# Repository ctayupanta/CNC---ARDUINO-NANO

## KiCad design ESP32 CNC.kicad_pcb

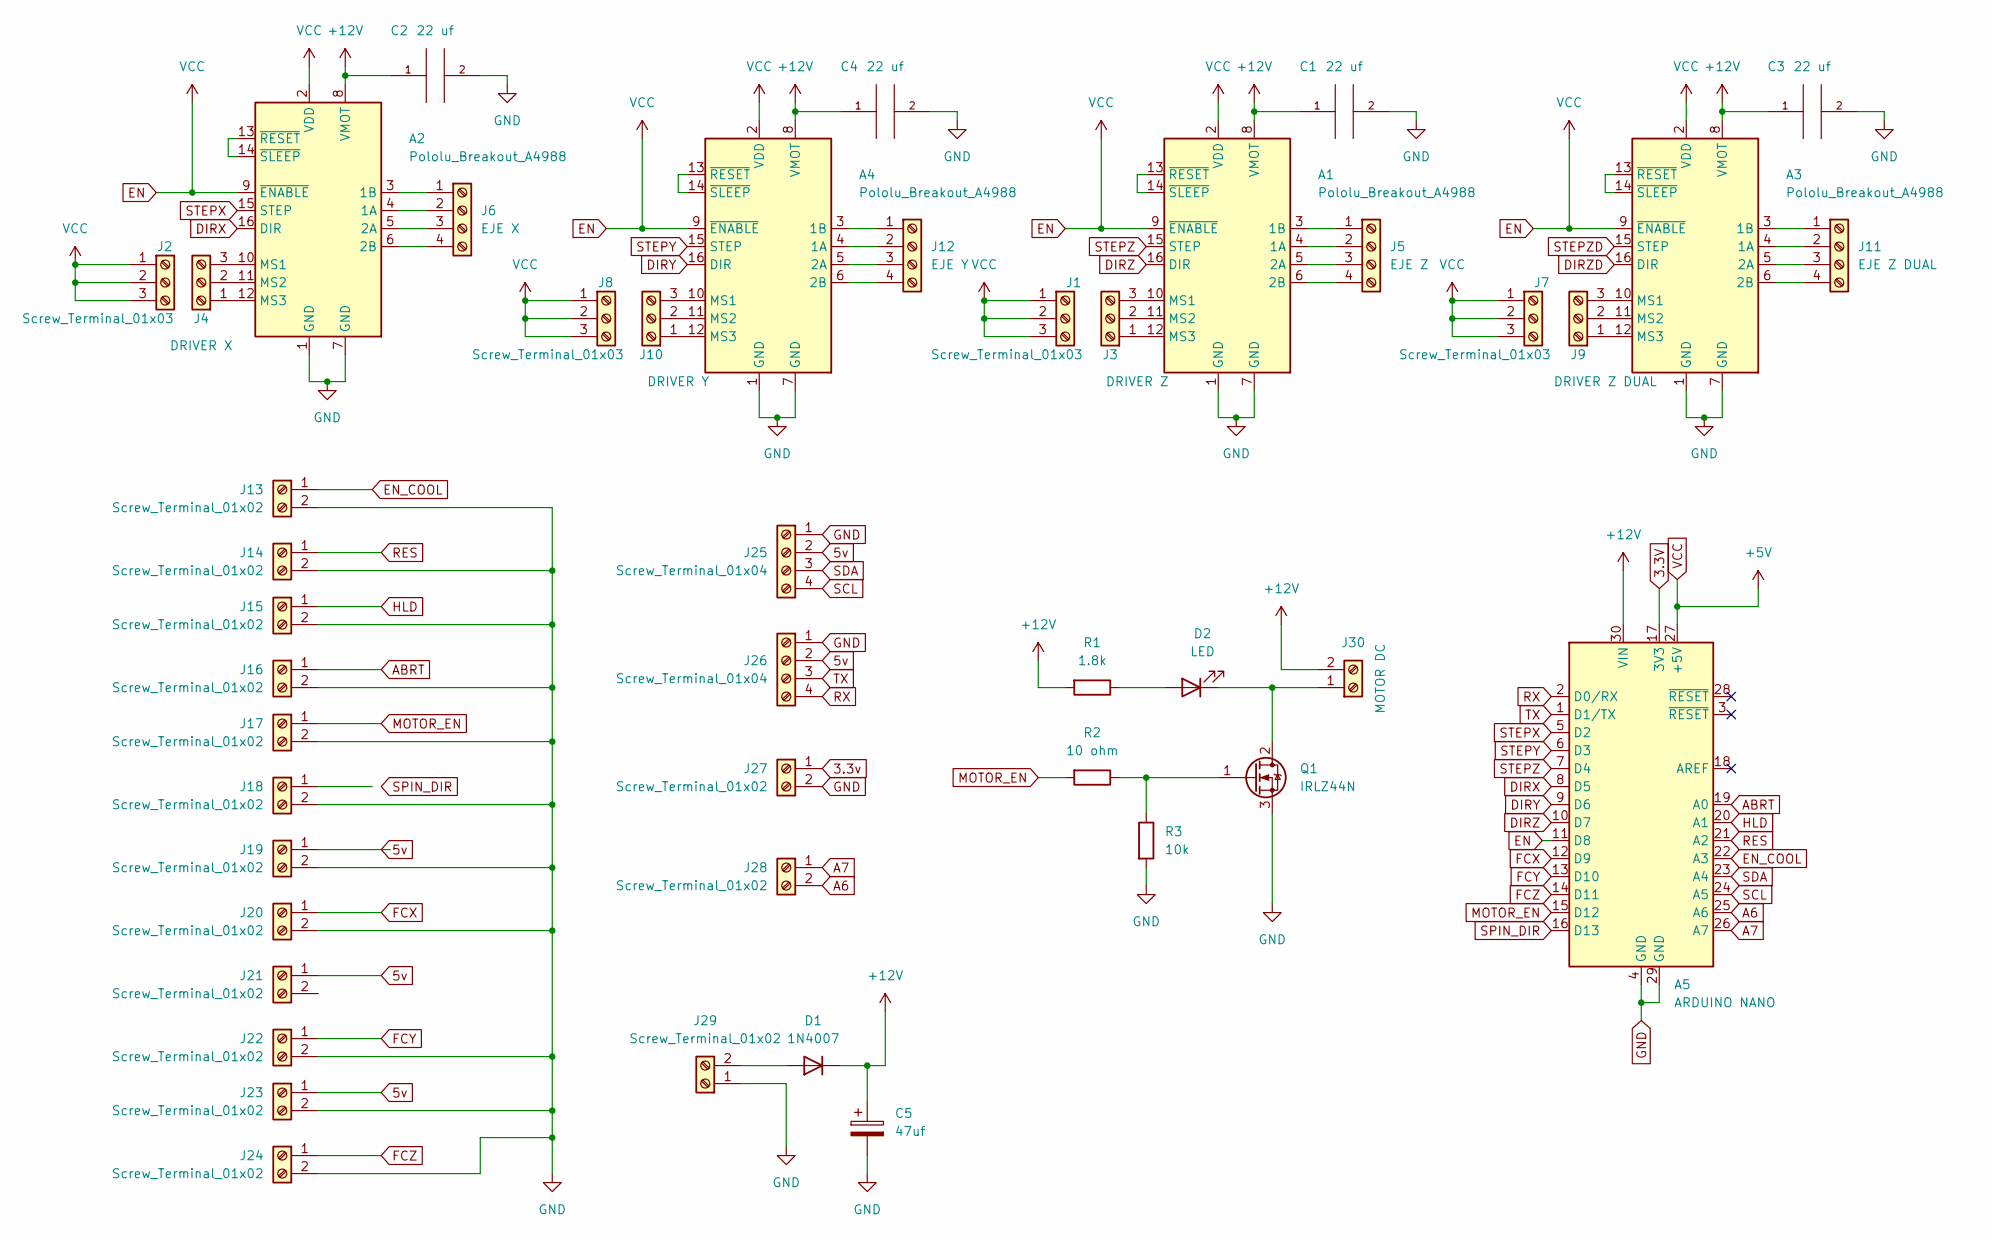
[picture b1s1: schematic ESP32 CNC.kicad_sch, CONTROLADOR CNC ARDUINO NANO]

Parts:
A1, A2, A3, A4: Pololu_Breakout_A4988; Pololu_Breakout-16_15.2x20.3mm
A5: ARDUINO NANO; Arduino_Nano
C1, C2, C3, C4: 22 uf; CP_Radial_D5.0mm_P2.50mm
C5: 47uf; CP_Radial_D5.0mm_P2.50mm
D1: 1N4007; D_DO-41_SOD81_P10.16mm_Horizontal
D2: LED; D_0805_2012Metric
J1, J2, J7, J8: Screw_Terminal_01x03; PinHeader_1x03_P2.54mm_Vertical
J3: DRIVER Z; PinHeader_1x03_P2.54mm_Vertical
J4: DRIVER X; PinHeader_1x03_P2.54mm_Vertical
J5: EJE Z; PinHeader_1x04_P2.54mm_Vertical
J6: EJE X; PinHeader_1x04_P2.54mm_Vertical
J9: DRIVER Z DUAL; PinHeader_1x03_P2.54mm_Vertical
J10: DRIVER Y; PinHeader_1x03_P2.54mm_Vertical
J11: EJE Z DUAL; PinHeader_1x04_P2.54mm_Vertical
J12: EJE Y; PinHeader_1x04_P2.54mm_Vertical
J13, J14, J15, J16, J17, J18, J19, J20, J21, J22, J23, J24, J27, J28, J29: Screw_Terminal_01x02; PinHeader_1x02_P2.54mm_Vertical
J25, J26: Screw_Terminal_01x04; PinHeader_1x04_P2.54mm_Vertical
J30: MOTOR DC; PinHeader_1x02_P2.54mm_Vertical
Q1: IRLZ44N; TO-220-3_Vertical
R1: 1.8k; R_0805_2012Metric
R2: 10 ohm; R_0805_2012Metric
R3: 10k; R_0805_2012Metric

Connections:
3.3v: J27.1
5v: J19.1, J21.1, J23.1, J25.2, J26.2
+12V: A1.8 (VMOT), A2.8 (VMOT), A3.8 (VMOT), A4.8 (VMOT), A5.30 (VIN), C1.1, C2.1, C3.1, C4.1, C5.1, D1.1 (K), J30.2, R1.2; also elsewhere on the board
A6: A5.25 (A6), J28.2; also elsewhere on the board
A7: A5.26 (A7), J28.1; also elsewhere on the board
ABRT: A5.19 (A0), J16.1; also elsewhere on the board
DIRX: A2.16 (DIR), A5.8 (D5); also elsewhere on the board
DIRY: A4.16 (DIR), A5.9 (D6); also elsewhere on the board
DIRZ: A1.16 (DIR), A5.10 (D7); also elsewhere on the board
DIRZD: A3.16 (DIR)
EN: A1.2 (VDD), A1.9 (~ENABLE), A2.2 (VDD), A2.9 (~ENABLE), A3.2 (VDD), A3.9 (~ENABLE), A4.2 (VDD), A4.9 (~ENABLE), A5.11 (D8), J1.1, J1.2, J1.3, J2.1, J2.2, J2.3, J7.1, J7.2, J7.3, J8.1, J8.2, J8.3; also elsewhere on the board
EN_COOL: A5.22 (A3), J13.1; also elsewhere on the board
FCX: A5.12 (D9), J20.1; also elsewhere on the board
FCY: A5.13 (D10), J22.1; also elsewhere on the board
FCZ: A5.14 (D11), J24.1; also elsewhere on the board
GND: A1.1 (GND), A1.7 (GND), A2.1 (GND), A2.7 (GND), A3.1 (GND), A3.7 (GND), A4.1 (GND), A4.7 (GND), A5.4 (GND), A5.29 (GND), C1.2, C2.2, C3.2, C4.2, C5.2, J13.2, J14.2, J15.2, J16.2, J17.2, J18.2, J19.2, J20.2, J22.2, J23.2, J24.2, J25.1, J26.1, J27.2, J29.1, Q1.3 (S), R3.2; also elsewhere on the board
HLD: A5.20 (A1), J15.1; also elsewhere on the board
MOTOR_EN: A5.15 (D12), J17.1, R2.2; also elsewhere on the board
unnamed: A1.3 (1B), J5.1
unnamed: A1.4 (1A), J5.2
unnamed: A1.5 (2A), J5.3
unnamed: A1.6 (2B), J5.4
unnamed: A1.10 (MS1), J3.3
unnamed: A1.11 (MS2), J3.2
unnamed: A1.12 (MS3), J3.1
unnamed: A1.13 (~RESET), A1.14 (~SLEEP)
unnamed: A2.3 (1B), J6.1
unnamed: A2.4 (1A), J6.2
unnamed: A2.5 (2A), J6.3
unnamed: A2.6 (2B), J6.4
unnamed: A2.10 (MS1), J4.3
unnamed: A2.11 (MS2), J4.2
unnamed: A2.12 (MS3), J4.1
unnamed: A2.13 (~RESET), A2.14 (~SLEEP)
unnamed: A3.3 (1B), J11.1
unnamed: A3.4 (1A), J11.2
unnamed: A3.5 (2A), J11.3
unnamed: A3.6 (2B), J11.4
unnamed: A3.10 (MS1), J9.3
unnamed: A3.11 (MS2), J9.2
unnamed: A3.12 (MS3), J9.1
unnamed: A3.13 (~RESET), A3.14 (~SLEEP)
unnamed: A4.3 (1B), J12.1
unnamed: A4.4 (1A), J12.2
unnamed: A4.5 (2A), J12.3
unnamed: A4.6 (2B), J12.4
unnamed: A4.10 (MS1), J10.3
unnamed: A4.11 (MS2), J10.2
unnamed: A4.12 (MS3), J10.1
unnamed: A4.13 (~RESET), A4.14 (~SLEEP)
unnamed: D1.2 (A), J29.2
unnamed 52: D2.1 (K), J30.1, Q1.2 (D); also elsewhere on the board
unnamed: D2.2 (A), R1.1
unnamed 54: Q1.1 (G), R2.1, R3.1; also elsewhere on the board
RES: A5.21 (A2), J14.1; also elsewhere on the board
RX: A5.2 (D0/RX), J26.4; also elsewhere on the board
SCL: A5.24 (A5), J25.4; also elsewhere on the board
SDA: A5.23 (A4), J25.3; also elsewhere on the board
STEPX: A2.15 (STEP), A5.5 (D2); also elsewhere on the board
STEPY: A4.15 (STEP), A5.6 (D3); also elsewhere on the board
STEPZ: A1.15 (STEP), A5.7 (D4); also elsewhere on the board
STEPZD: A3.15 (STEP)
TX: A5.1 (D1/TX), J26.3; also elsewhere on the board

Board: 2 copper layers, 46 parts (0 on the bottom side), 60 nets, no tracks yet.

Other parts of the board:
Arduino Nano: ARDUINO NANO; Arduino_Nano
IRLZ44N: IRLZ44N; TO-220-3_Vertical
MOTOR DC: MOTOR DC; PinHeader_1x02_P2.54mm_Vertical

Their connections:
+12V: Arduino Nano.30 (VIN), MOTOR DC.2; also elsewhere on the board
A6: Arduino Nano.25 (A6); also elsewhere on the board
A7: Arduino Nano.26 (A7); also elsewhere on the board
ABRT: Arduino Nano.19 (A0); also elsewhere on the board
DIRX: Arduino Nano.8 (D5); also elsewhere on the board
DIRY: Arduino Nano.9 (D6); also elsewhere on the board
DIRZ: Arduino Nano.10 (D7); also elsewhere on the board
EN: Arduino Nano.11 (D8), Arduino Nano.27 (+5V); also elsewhere on the board
EN_COOL: Arduino Nano.22 (A3); also elsewhere on the board
FCX: Arduino Nano.12 (D9); also elsewhere on the board
FCY: Arduino Nano.13 (D10); also elsewhere on the board
FCZ: Arduino Nano.14 (D11); also elsewhere on the board
GND: Arduino Nano.4 (GND), Arduino Nano.29 (GND), IRLZ44N.3 (S); also elsewhere on the board
HLD: Arduino Nano.20 (A1); also elsewhere on the board
MOTOR_EN: Arduino Nano.15 (D12); also elsewhere on the board
unnamed 52: IRLZ44N.2 (D), MOTOR DC.1; also elsewhere on the board
unnamed 54: IRLZ44N.1 (G); also elsewhere on the board
RES: Arduino Nano.21 (A2); also elsewhere on the board
RX: Arduino Nano.2 (D0/RX); also elsewhere on the board
SCL: Arduino Nano.24 (A5); also elsewhere on the board
SDA: Arduino Nano.23 (A4); also elsewhere on the board
STEPX: Arduino Nano.5 (D2); also elsewhere on the board
STEPY: Arduino Nano.6 (D3); also elsewhere on the board
STEPZ: Arduino Nano.7 (D4); also elsewhere on the board
TX: Arduino Nano.1 (D1/TX); also elsewhere on the board

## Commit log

2022-10-04 Controlador de CNC
